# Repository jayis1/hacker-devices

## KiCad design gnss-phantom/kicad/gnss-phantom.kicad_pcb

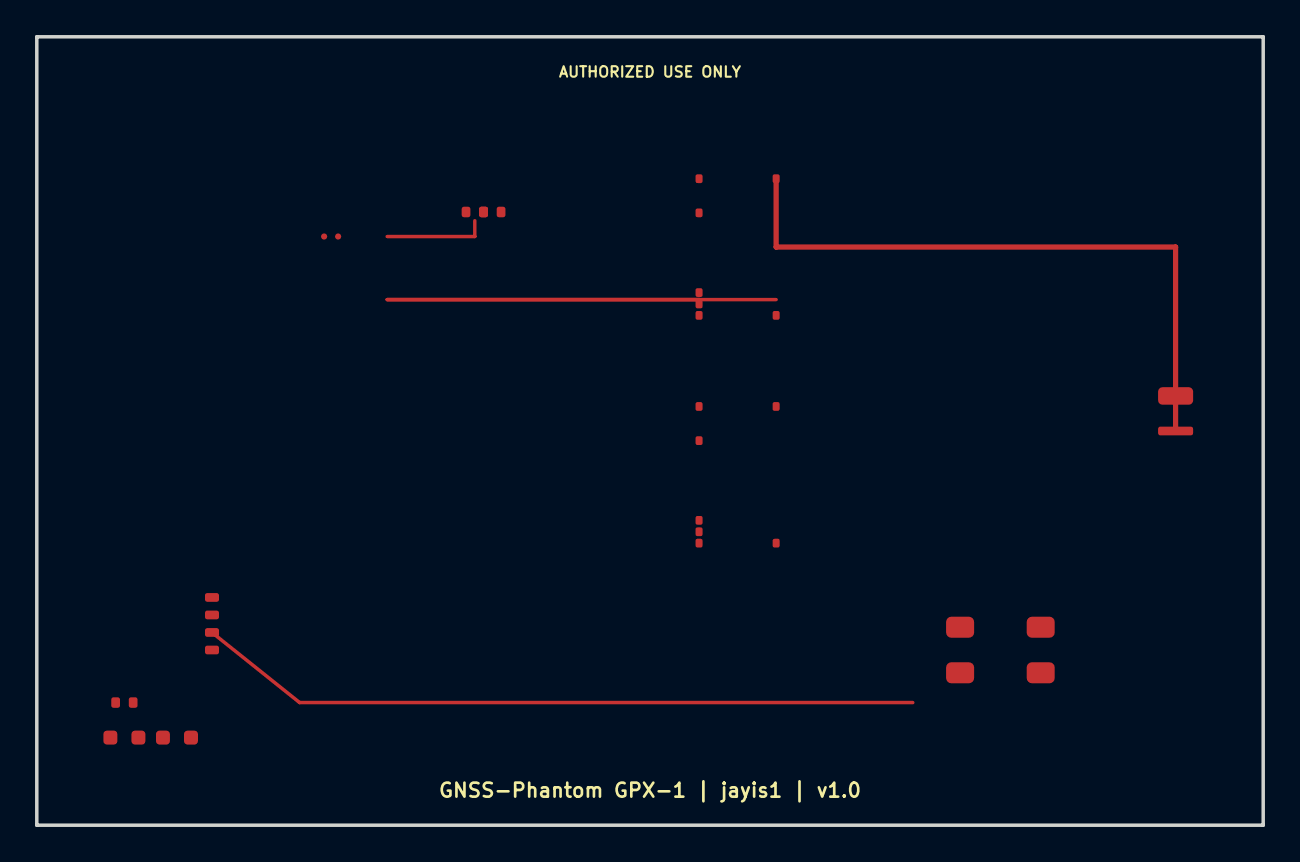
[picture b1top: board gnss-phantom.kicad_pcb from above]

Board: 4 copper layers, 70.0 x 45.0 mm, 11 parts (0 on the bottom side), 7 nets.

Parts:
C1, C2: 100nF; C_0402
D1: LED_Blue; LED_0603
D2: LED_Red; LED_0603
J1: SMA; SMA_Amphenol_132289_Edge_Mount
R1: 1k; R_0402
U1: STM32H743VIT6; TFBGA-100_8x8mm_P0.8mm
U2, U3: Si4463; SSOP-20_4.4x6.5mm_P0.65mm
U4: nRF52840-M.2; Nordic_M.2
Y1: TG5032CE-26N; Oscillator_SMD_TCXO_5032_4Pins

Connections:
+3V3: C1.1, C2.1, R1.2, U1.A1, U2.4, U3.4, U4.1, Y1.1
GND: C1.2, C2.2, D1.2, D2.2, J1.2, U1.A2, U4.2, Y1.2, Y1.4
LED_STATUS: D1.1, R1.1
RF_TX: J1.1, U2.20
SPI2_MISO: U2.14, U3.14
SPI2_MOSI: U2.13, U3.13
SPI2_SCLK: U2.12, U3.12

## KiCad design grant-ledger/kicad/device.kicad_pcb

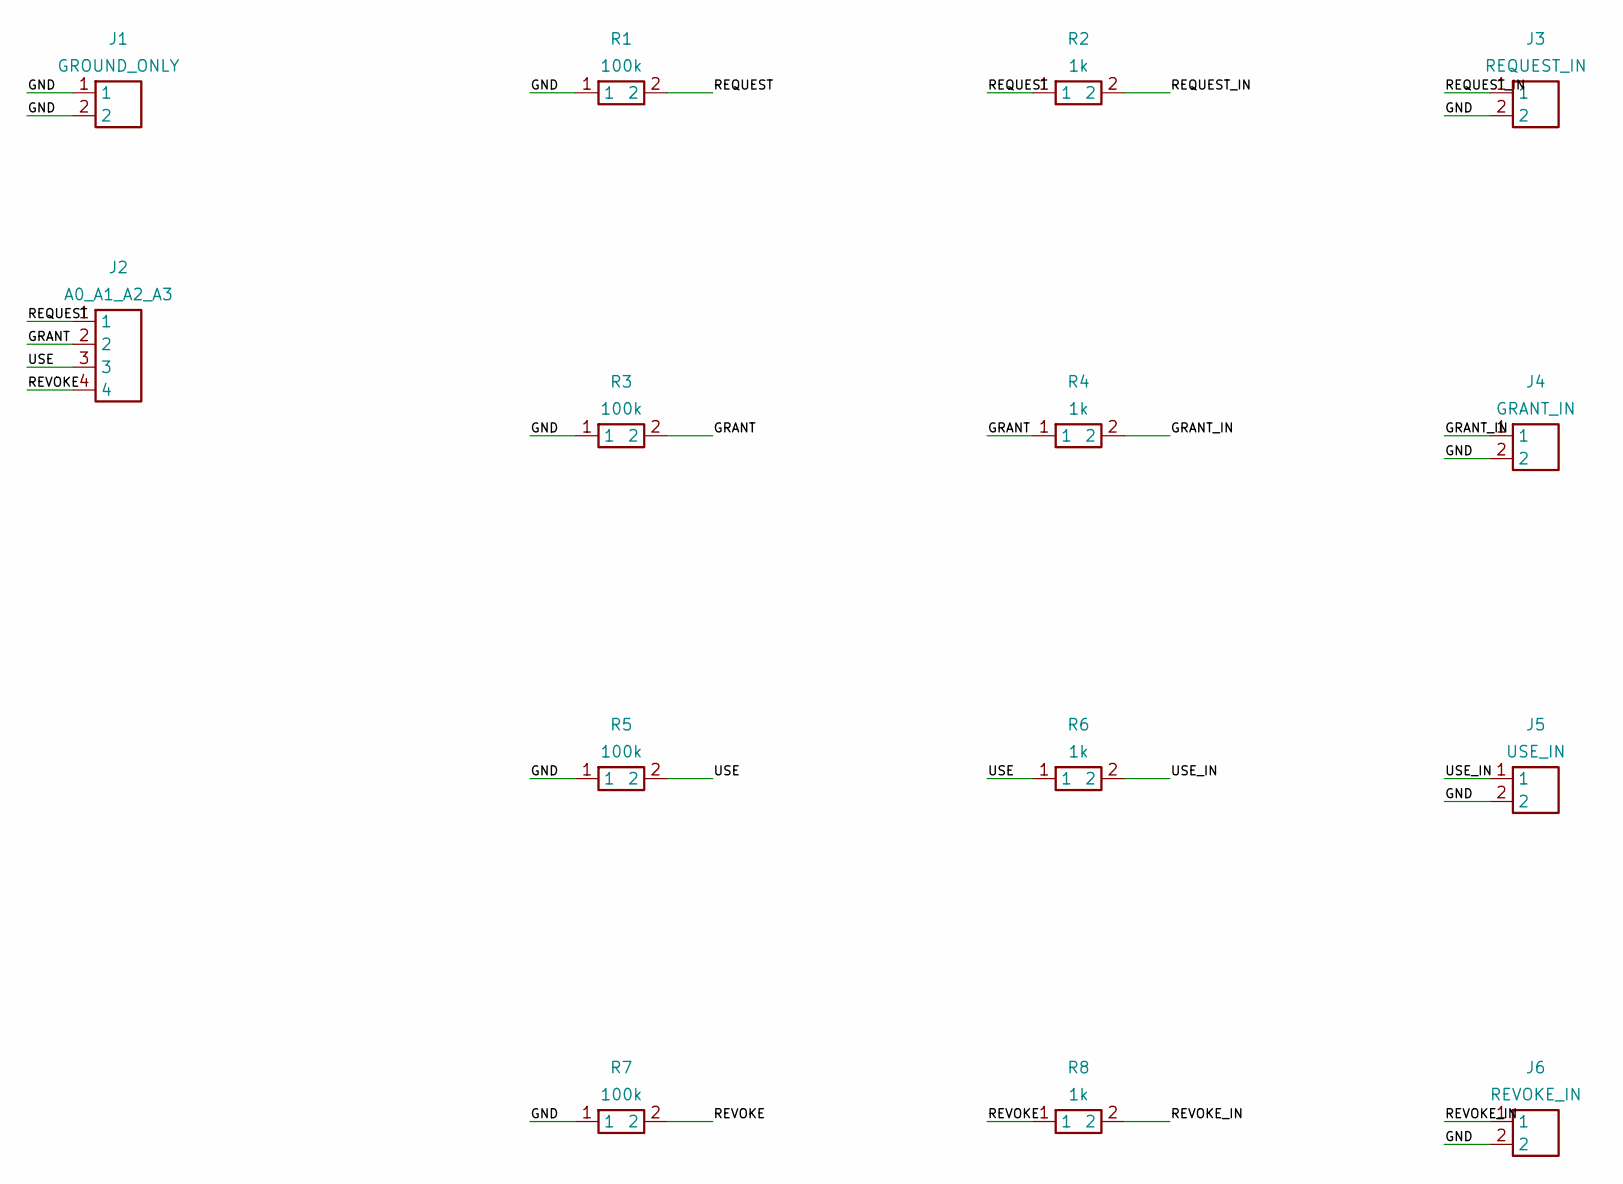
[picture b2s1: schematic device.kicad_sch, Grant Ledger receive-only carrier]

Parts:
J1: GROUND_ONLY; PinHeader_1x02_P2.54mm_Vertical
J2: A0_A1_A2_A3; PinHeader_1x04_P2.54mm_Vertical
J3: REQUEST_IN; PinHeader_1x02_P2.54mm_Vertical
J4: GRANT_IN; PinHeader_1x02_P2.54mm_Vertical
J5: USE_IN; PinHeader_1x02_P2.54mm_Vertical
J6: REVOKE_IN; PinHeader_1x02_P2.54mm_Vertical
R1, R3, R5, R7: 100k; R_Axial_DIN0207_L6.3mm_D2.5mm_P7.62mm_Horizontal
R2, R4, R6, R8: 1k; R_Axial_DIN0207_L6.3mm_D2.5mm_P7.62mm_Horizontal

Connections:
GND: J1.1, J1.2, J3.2, J4.2, J5.2, J6.2, R1.1, R3.1, R5.1, R7.1
GRANT: J2.2, R3.2, R4.1
GRANT_IN: J4.1, R4.2
REQUEST: J2.1, R1.2, R2.1
REQUEST_IN: J3.1, R2.2
REVOKE: J2.4, R7.2, R8.1
REVOKE_IN: J6.1, R8.2
USE: J2.3, R5.2, R6.1
USE_IN: J5.1, R6.2

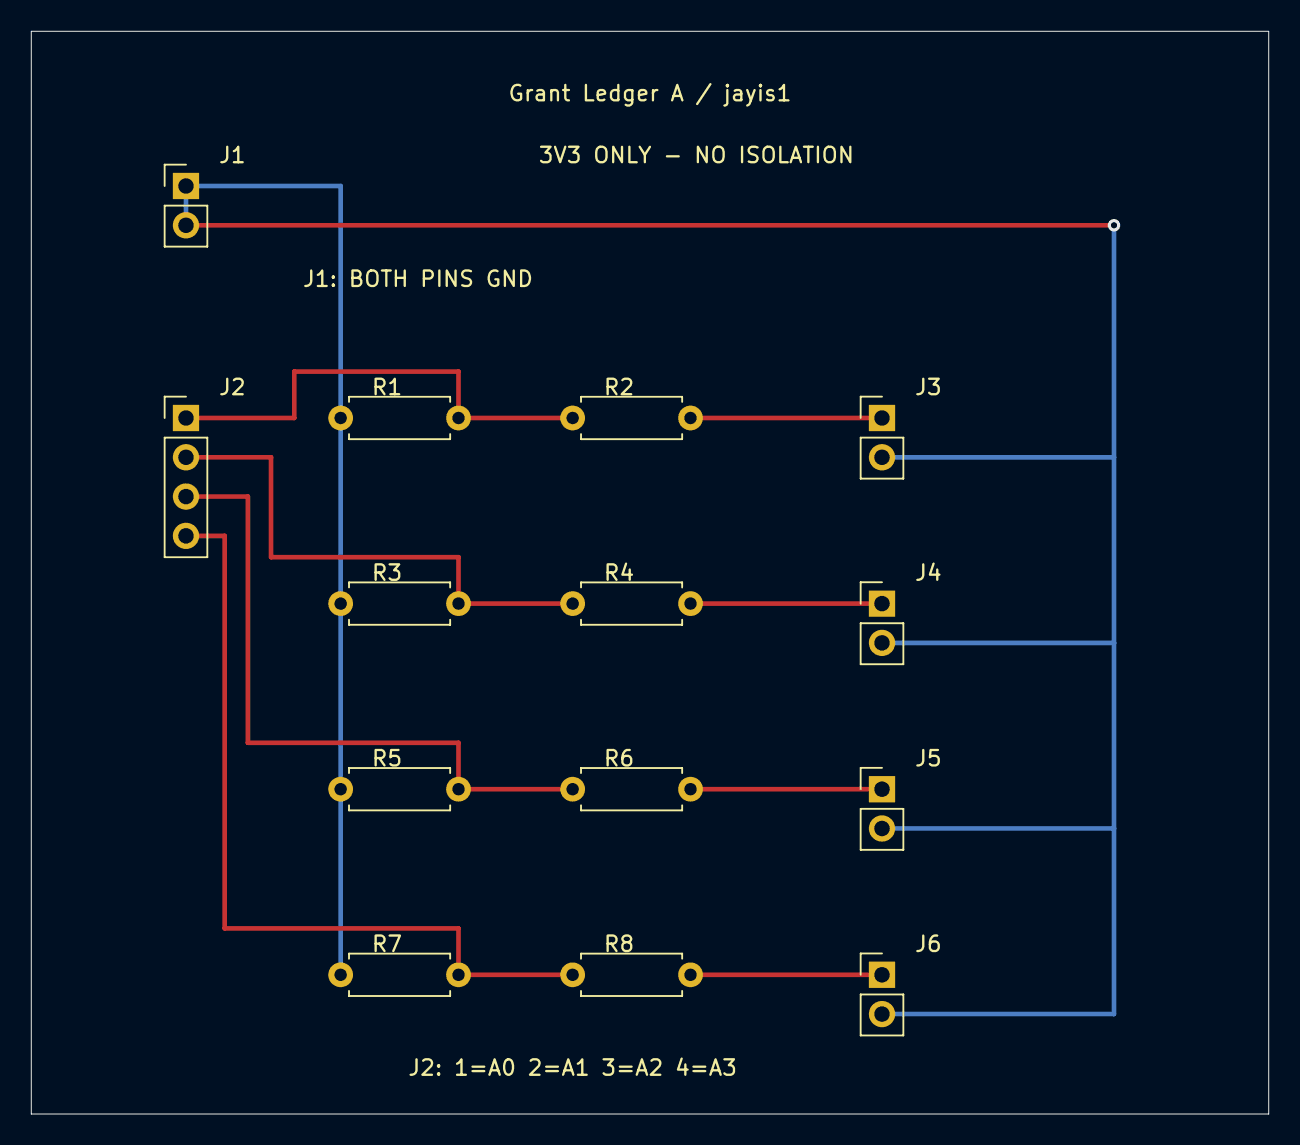
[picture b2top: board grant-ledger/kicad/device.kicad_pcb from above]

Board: 2 copper layers, 80.0 x 70.0 mm, 14 parts (0 on the bottom side), 9 nets.

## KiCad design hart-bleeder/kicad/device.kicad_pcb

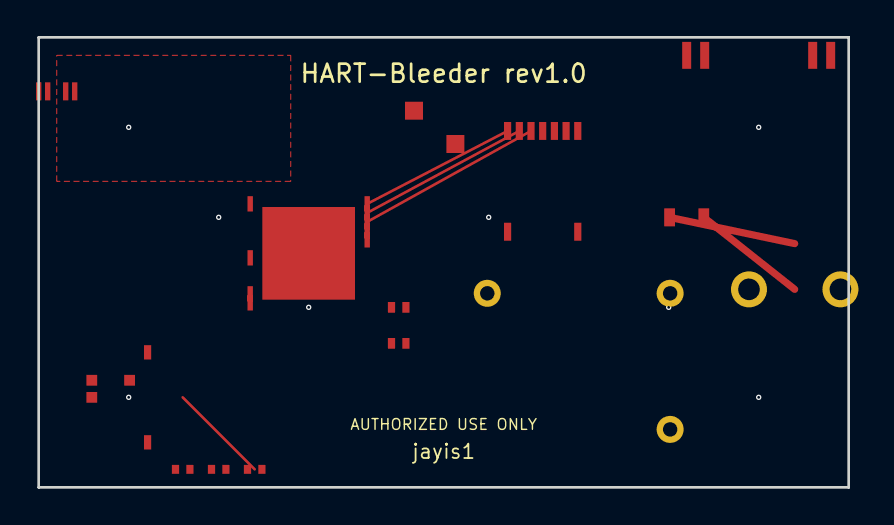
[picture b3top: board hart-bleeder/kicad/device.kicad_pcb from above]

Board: 2 copper layers, 45.0 x 25.0 mm, 15 parts (0 on the bottom side), 11 nets.

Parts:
C1: 10uF; C_0603_1608Metric
C2: 100nF; C_0603_1608Metric
D1: RED; LED_0603_1608Metric
D2: GREEN; LED_0603_1608Metric
D3: BLUE; LED_0603_1608Metric
J1: USB-C_2.0; USB_C_Receptacle_Amphenol_12401610E4-2A
J2: Micro_SD; microSD_HC_Hirose_DM3AT-SF-PEJM5
J3: LOOP_TERM; TerminalBlock_bornier-2_P5.08mm
K1: G6K-2F-Y-DC3; Relay_DPDT_Omron_G6K-2F
R5: 250R_0.1%; R_0805_2012Metric
U1: STM32G474CEU6; QFN-48-1EP_7x7mm_P0.5mm_EP5.15x5.15mm
U2: MAX13440EETD+; TSSOP-14_4.4x5mm_P0.65mm
U5: TPS63020DSJR; TI_DSJ-14
U6: MCP73831T-2ACI/OT; SOT-23-5
Y1: 24MHz; Crystal_SMD_3225-4Pin_3.2x2.5mm

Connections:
+3V3: C1.1, C2.1, J2.8, U1.1, U2.1, U2.14, U5.14
GND: C1.2, C2.2, D1.2, D2.2, D3.2, J1.A1, U1.EXP, U2.7, U2.8, U6.2
HART_CD_N: U1.47, U2.4
HART_RTS_N: U1.46, U2.3
HART_SHDN_N: U1.48, U2.2
LOOP_IN: J3.1, K1.4
LOOP_OUT: J3.2, K1.8
USART2_RX: U1.45, U2.5
USART2_TX: U1.44, U2.6
VBAT: U5.1, U6.3
VUSB: J1.A4, U6.1

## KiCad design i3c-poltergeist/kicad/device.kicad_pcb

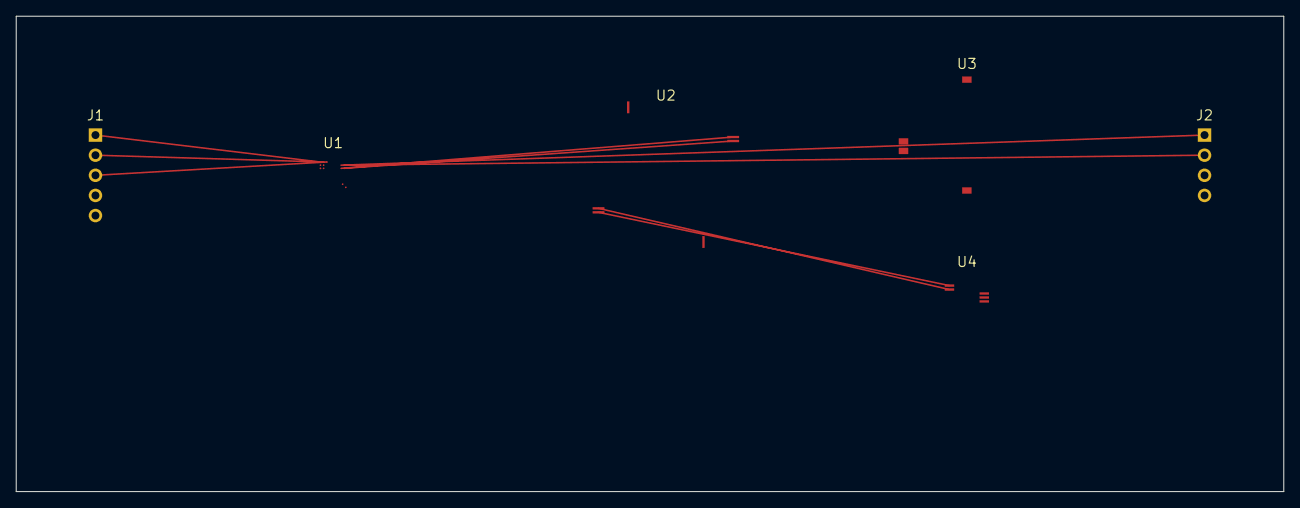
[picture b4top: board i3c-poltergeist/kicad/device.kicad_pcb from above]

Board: 2 copper layers, 160.0 x 60.0 mm, 6 parts (0 on the bottom side), 11 nets.

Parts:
J1: HOST_I3C_CLIP; PinHeader_1x08_P2.54mm_Vertical
J2: TARGET_I3C_CLIP; PinHeader_1x08_P2.54mm_Vertical
U1: LIFCL-17; WLCSP-81_3.684x3.818mm_Layout9x9_P0.4mm
U2: STM32H735RGV6; LQFP-100_14x14mm_P0.5mm
U3: ESP32-C6-MINI-1
U4: INA238AIDGSR; VSSOP-10_3x3mm_P0.5mm

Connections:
3V3: J1.4, J2.3, U1.H8, U2.13, U3.1, U4.6, U4.8
GND: J1.5, J2.4, U1.J9, U2.64, U3.15, U4.5
I2C_SCL: U2.95, U4.1
I2C_SDA: U2.96, U4.2
PULL_OD: J1.3, U1.A3
SCL_HOST: J1.1, U1.A1
SCL_TGT: J2.1, U1.B1
SDA_HOST: J1.2, U1.A2
SDA_TGT: J2.2, U1.B2
UART_RX: U1.C2, U2.26, U3.31
UART_TX: U1.C1, U2.25, U3.30

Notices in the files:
harmonic-reaper/kicad/device.kicad_sch:
License: GPL-2.0
